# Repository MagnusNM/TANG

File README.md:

# TANG
Like RAMPS but for dumb shit

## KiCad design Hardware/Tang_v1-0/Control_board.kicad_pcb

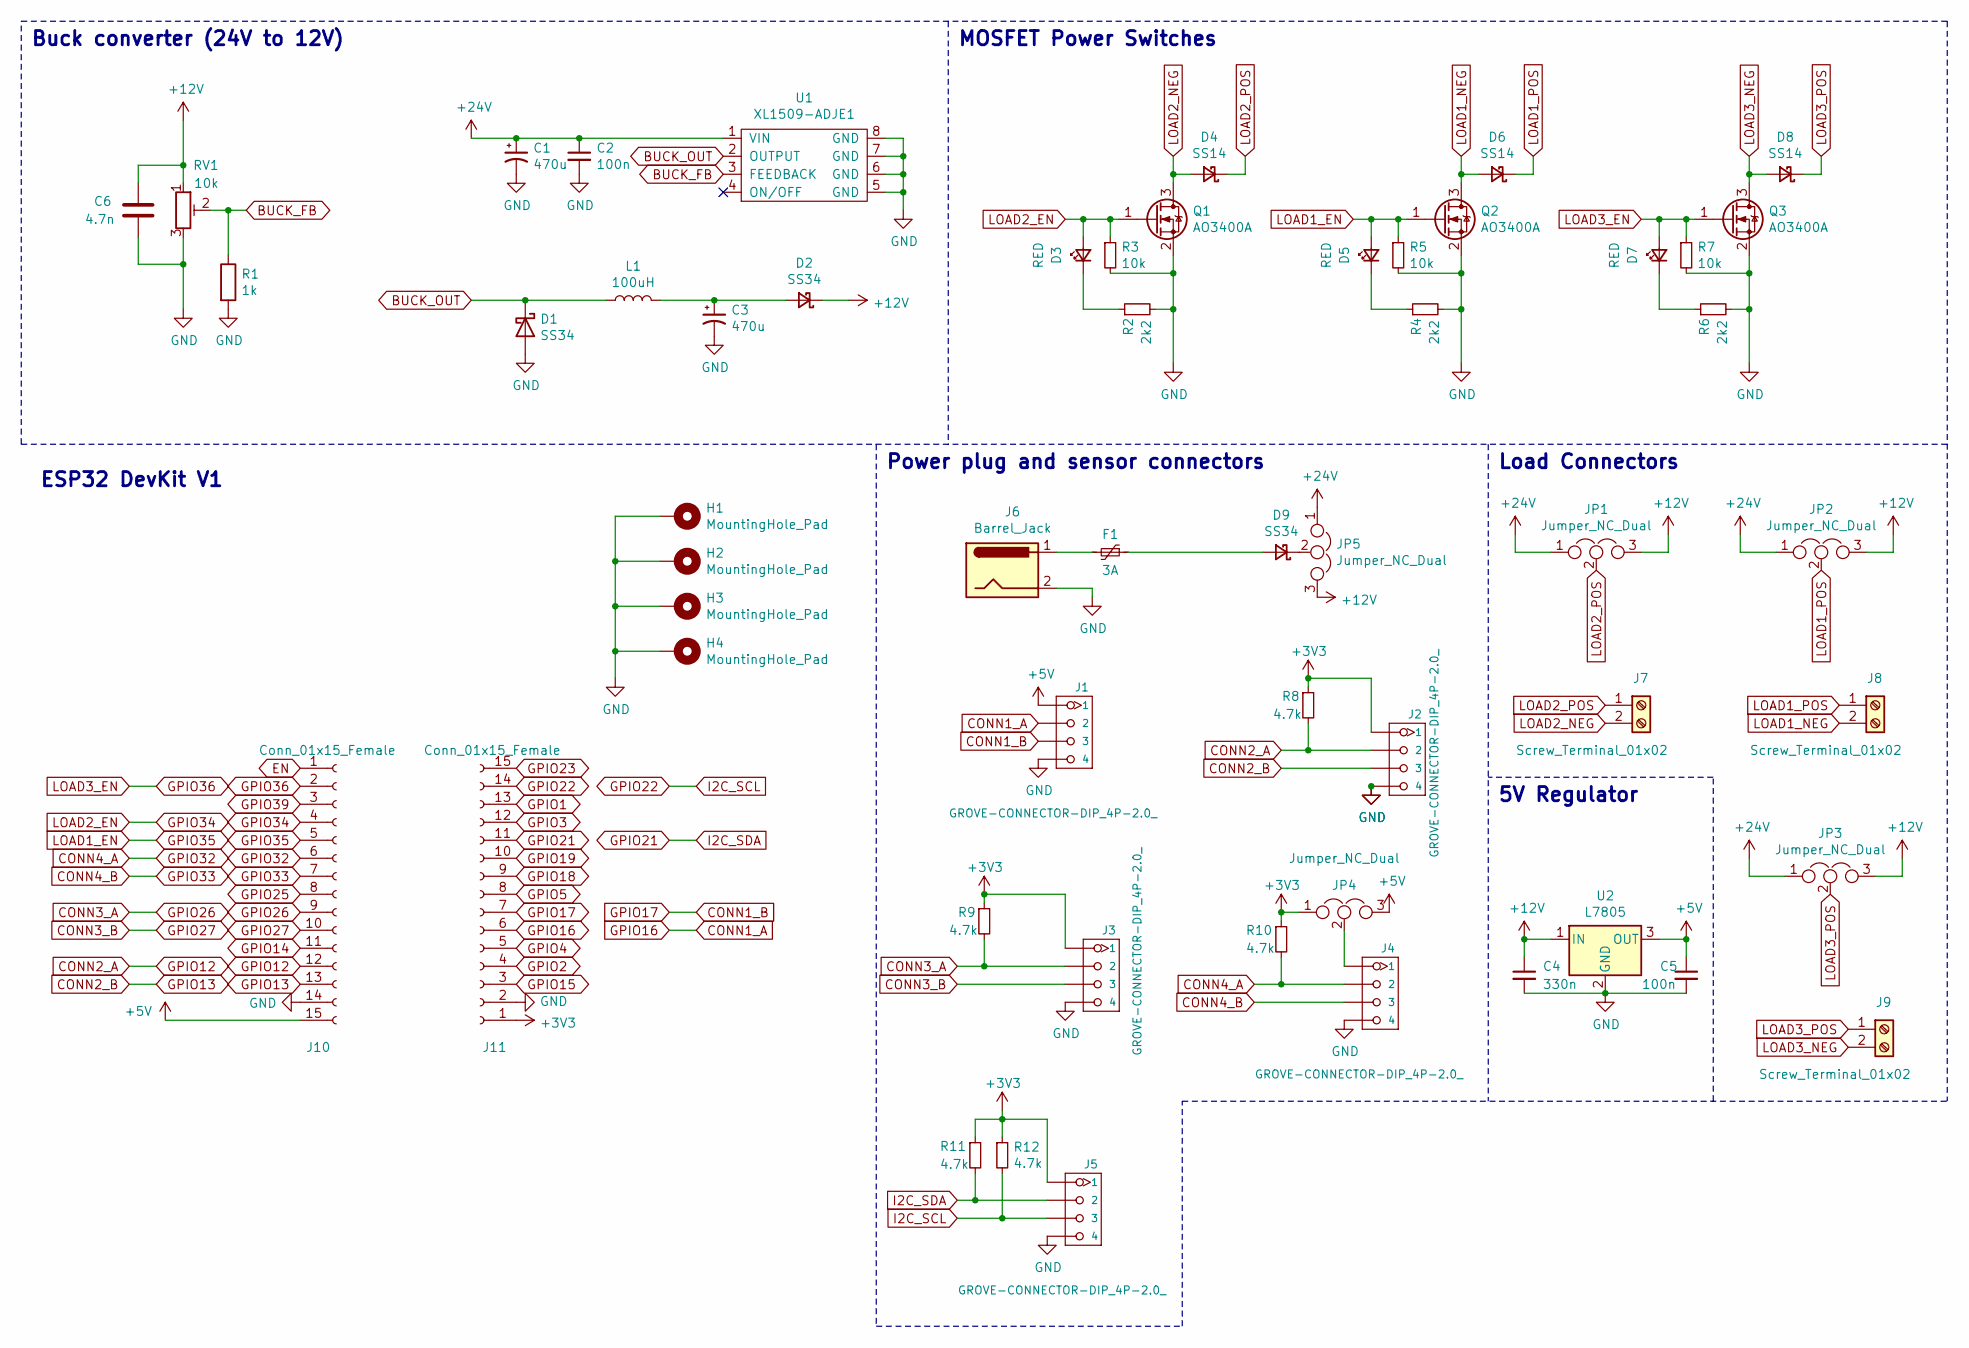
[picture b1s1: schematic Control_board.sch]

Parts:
C1, C3: 470u; C_Elec_10x10.2; LCSC Part # C3350
C2: 100n; C_0603_1608Metric; LCSC Part # C14663
C4: 330n; C_0805_2012Metric; LCSC Part # C1740
C5: 100n; C_0805_2012Metric; LCSC Part # C49678
C6: 4.7n; C_0402_1005Metric; LCSC Part # C1538
D1, D2, D9: SS34; D_SMA; LCSC Part # C8678
D3, D5, D7: RED; LED_0603_1608Metric; LCSC Part # C2286
D4, D6, D8: SS14; D_SMA; LCSC Part # C2480
F1: 3A; Fuse_1812_4532Metric; LCSC Part # C32404
H1, H2, H3, H4: MountingHole_Pad; MountingHole_3.2mm_M3_Pad_Via
J1, J2, J3, J4, J5: GROVE-CONNECTOR-DIP_4P-2.0_; NS-Tech_Grove_1x04_P2mm_Vertical
J6: Barrel_Jack; BarrelJack_Horizontal
J7, J8, J9: Screw_Terminal_01x02; TerminalBlock_Phoenix_MPT-0,5-2-2.54_1x02_P2.54mm_Horizontal
J10, J11: Conn_01x15_Female; PinSocket_1x15_P2.54mm_Vertical
JP1, JP2, JP3, JP4, JP5: Jumper_NC_Dual; PinHeader_1x03_P2.54mm_Vertical
L1: 100uH; Wuerth_7447211101; LCSC Part # C429814
Q1, Q2, Q3: AO3400A; SOT-23; LCSC Part # C344010
R1: 1k; R_0603_1608Metric; LCSC Part # C21190
R2, R4, R6: 2k2; R_0603_1608Metric; LCSC Part # C4190
R3, R5, R7: 10k; R_0603_1608Metric; LCSC Part # C25804
R8, R9, R10, R11, R12: 4.7k; R_0402_1005Metric; LCSC Part # C25900
RV1: 10k; Potentiometer_Bourns_3296P_Horizontal
U1: XL1509-ADJE1; SOP-8_3.9x4.9mm_P1.27mm; LCSC Part # C74192
U2: L7805; TO-263-2; LCSC Part # C15077

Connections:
+3V3: J2.1, J3.1, J5.1, J11.1, JP4.1, R8.1, R9.1, R10.1, R11.1, R12.1
+5V: C5.1, J1.1, J10.15, JP4.3, U2.3 (OUT)
+12V: C4.1, C6.1, D2.1 (K), JP1.3, JP2.3, JP3.3, JP5.3, RV1.1, U2.1 (IN)
+24V: C1.1, C2.1, JP1.1, JP2.1, JP3.1, JP5.1, U1.1 (VIN)
BUCK_FB: R1.1, RV1.2, U1.3 (FEEDBACK)
BUCK_OUT: D1.1 (K), L1.1, L1.3, U1.2 (OUTPUT)
CONN1_A: J1.2, J11.6
CONN1_B: J1.3, J11.7
CONN2_A: J2.2, J10.12, R8.2
CONN2_B: J2.3, J10.13
CONN3_A: J3.2, J10.9, R9.2
CONN3_B: J3.3, J10.10
CONN4_A: J4.2, J10.6, R10.2
CONN4_B: J4.3, J10.7
EN: J10.1
GND: C1.2, C2.2, C3.2, C4.2, C5.2, C6.2, D1.2 (A), H1.1, H2.1, H3.1, H4.1, J1.4, J2.4, J3.4, J4.4, J5.4, J6.2, J10.14, J11.2, Q1.2 (S), Q2.2 (S), Q3.2 (S), R1.2, R2.2, R3.2, R4.2, R5.2, R6.2, R7.2, RV1.3, U1.5 (GND), U1.6 (GND), U1.7 (GND), U1.8 (GND), U2.2 (GND)
GPIO1: J11.13
GPIO2: J11.4
GPIO3: J11.12
GPIO4: J11.5
GPIO5: J11.8
GPIO14: J10.11
GPIO15: J11.3
GPIO18: J11.9
GPIO19: J11.10
GPIO21: J5.2, J11.11, R11.2
GPIO22: J5.3, J11.14, R12.2
GPIO23: J11.15
GPIO25: J10.8
GPIO34: D3.2 (A), J10.4, Q1.1 (G), R3.1
GPIO35: D5.2 (A), J10.5, Q2.1 (G), R5.1
GPIO36: D7.2 (A), J10.2, Q3.1 (G), R7.1
GPIO39: J10.3
LOAD1_NEG: D6.2 (A), J8.2, Q2.3 (D)
LOAD1_POS: D6.1 (K), J8.1, JP2.2
LOAD2_NEG: D4.2 (A), J7.2, Q1.3 (D)
LOAD2_POS: D4.1 (K), J7.1, JP1.2
LOAD3_NEG: D8.2 (A), J9.2, Q3.3 (D)
LOAD3_POS: D8.1 (K), J9.1, JP3.2
unnamed: C3.1, D2.2 (A), L1.2
unnamed: D3.1 (K), R2.1
unnamed: D5.1 (K), R4.1
unnamed: D7.1 (K), R6.1
unnamed: D9.1 (K), JP5.2
unnamed: D9.2 (A), F1.1
unnamed: F1.2, J6.1
unnamed: J4.1, JP4.2

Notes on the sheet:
Buck converter (24V to 12V)
MOSFET Power Switches
Load Connectors
5V Regulator
Power plug and sensor connectors
ESP32 DevKit V1

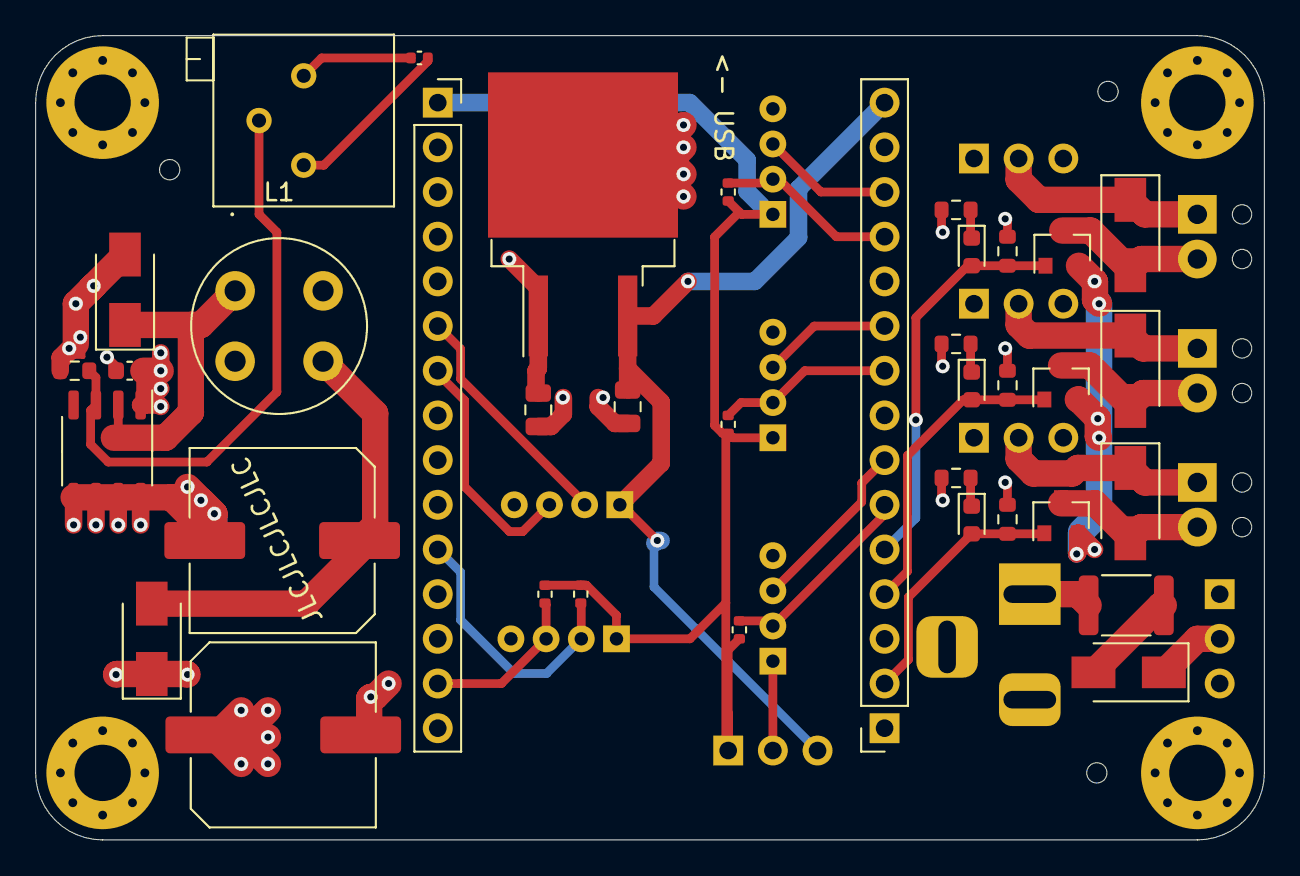
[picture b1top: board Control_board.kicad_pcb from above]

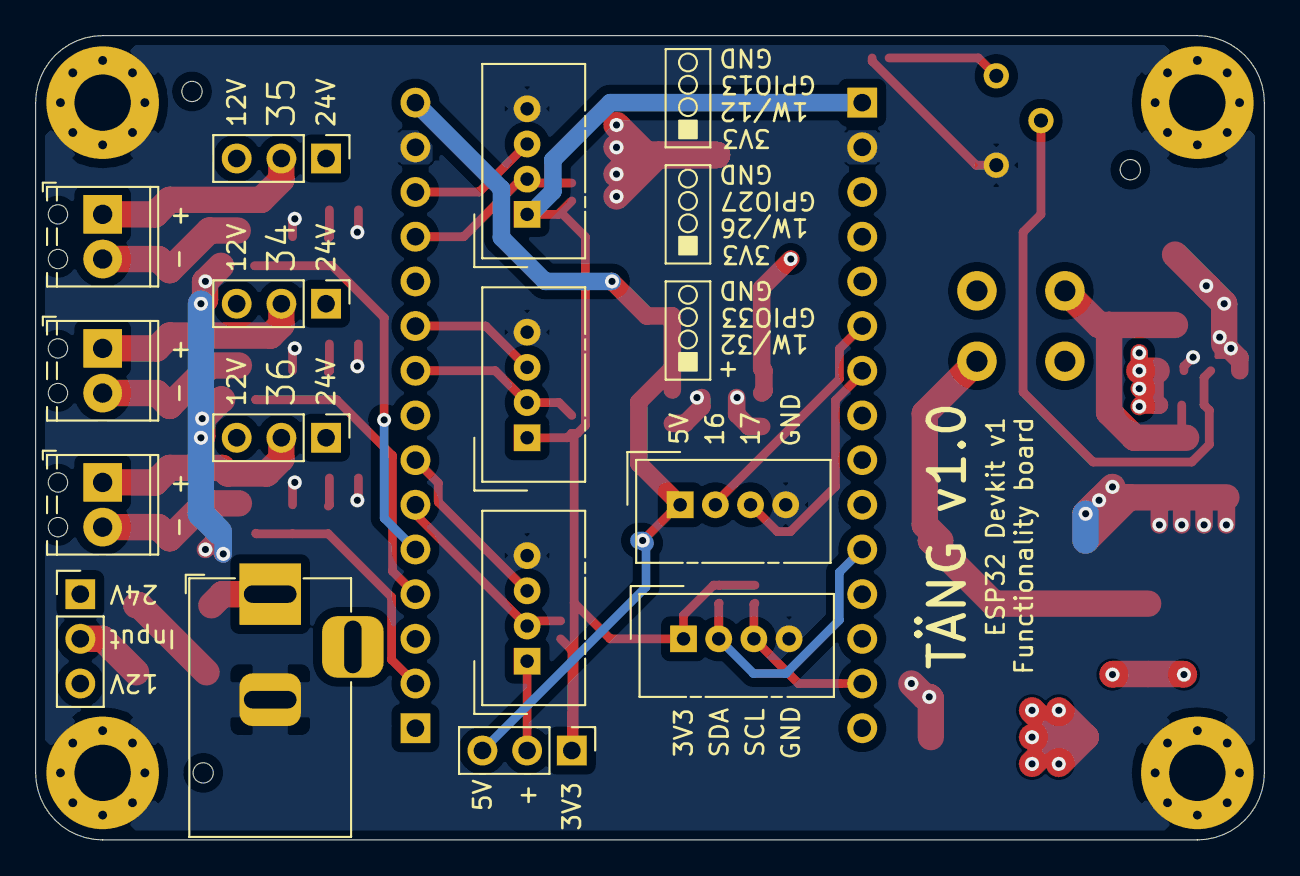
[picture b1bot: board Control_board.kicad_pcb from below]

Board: 4 copper layers, 69.8 x 45.7 mm, 55 parts (14 on the bottom side), 34 nets.

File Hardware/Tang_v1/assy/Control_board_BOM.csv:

Comment,Designator,Footprint,LCSC
470u,"C1,C3",Capacitor_SMD:C_Elec_10x10.2,C3350
100n,C2,Capacitor_SMD:C_0603_1608Metric,C14663
330n,C4,Capacitor_SMD:C_0805_2012Metric,C1740
100n,C5,Capacitor_SMD:C_0805_2012Metric,C49678
4.7n,C6,Capacitor_SMD:C_0402_1005Metric,C1538
RED,"D3,D5,D7",LED_SMD:LED_0603_1608Metric,C2286
SS14,"D4,D6,D8",Diode_SMD:D_SMA,C2480
SS34,"D1,D2,D9",Diode_SMD:D_SMA,C8678
3A,F1,Fuse:Fuse_1812_4532Metric,C32404
MountingHole_Pad,"H1,H2,H3,H4",MountingHole:MountingHole_3.2mm_M3_Pad_Via,
Conn_01x15_Female,"J10,J11",Connector_PinSocket_2.54mm:PinSocket_1x15_P2.54mm_Vertical,
GROVE-CONNECTOR-DIP_4P-2.0_,"J1,J2,J3,J4,J5",Connector:NS-Tech_Grove_1x04_P2mm_Vertical,
Barrel_Jack,J6,Connector_BarrelJack:BarrelJack_Horizontal,
Screw_Terminal_01x02,"J7,J8,J9","TerminalBlock_Phoenix:TerminalBlock_Phoenix_MPT-0,5-2-2.54_1x02_P2.54mm_Horizontal",
Jumper_NC_Dual,"JP1,JP2,JP3,JP4,JP5",Connector_PinHeader_2.54mm:PinHeader_1x03_P2.54mm_Vertical,
100uH,L1,RasmusKiCadLibrary:Wuerth_7447211101,
AO3400A,"Q1,Q2,Q3",Package_TO_SOT_SMD:SOT-23,C344010
1k,R1,Resistor_SMD:R_0603_1608Metric,C21190
4.7k,"R8,R9,R10,R11,R12",Resistor_SMD:R_0402_1005Metric,C25900
2k2,"R2,R4,R6",Resistor_SMD:R_0603_1608Metric,C4190
10k,"R3,R5,R7",Resistor_SMD:R_0603_1608Metric,C25804
10k,RV1,Potentiometer_THT:Potentiometer_Bourns_3296P_Horizontal,
XL1509-ADJE1,U1,Package_SO:SOP-8_3.9x4.9mm_P1.27mm,C74192
L7805,U2,Package_TO_SOT_SMD:TO-263-2,C15077

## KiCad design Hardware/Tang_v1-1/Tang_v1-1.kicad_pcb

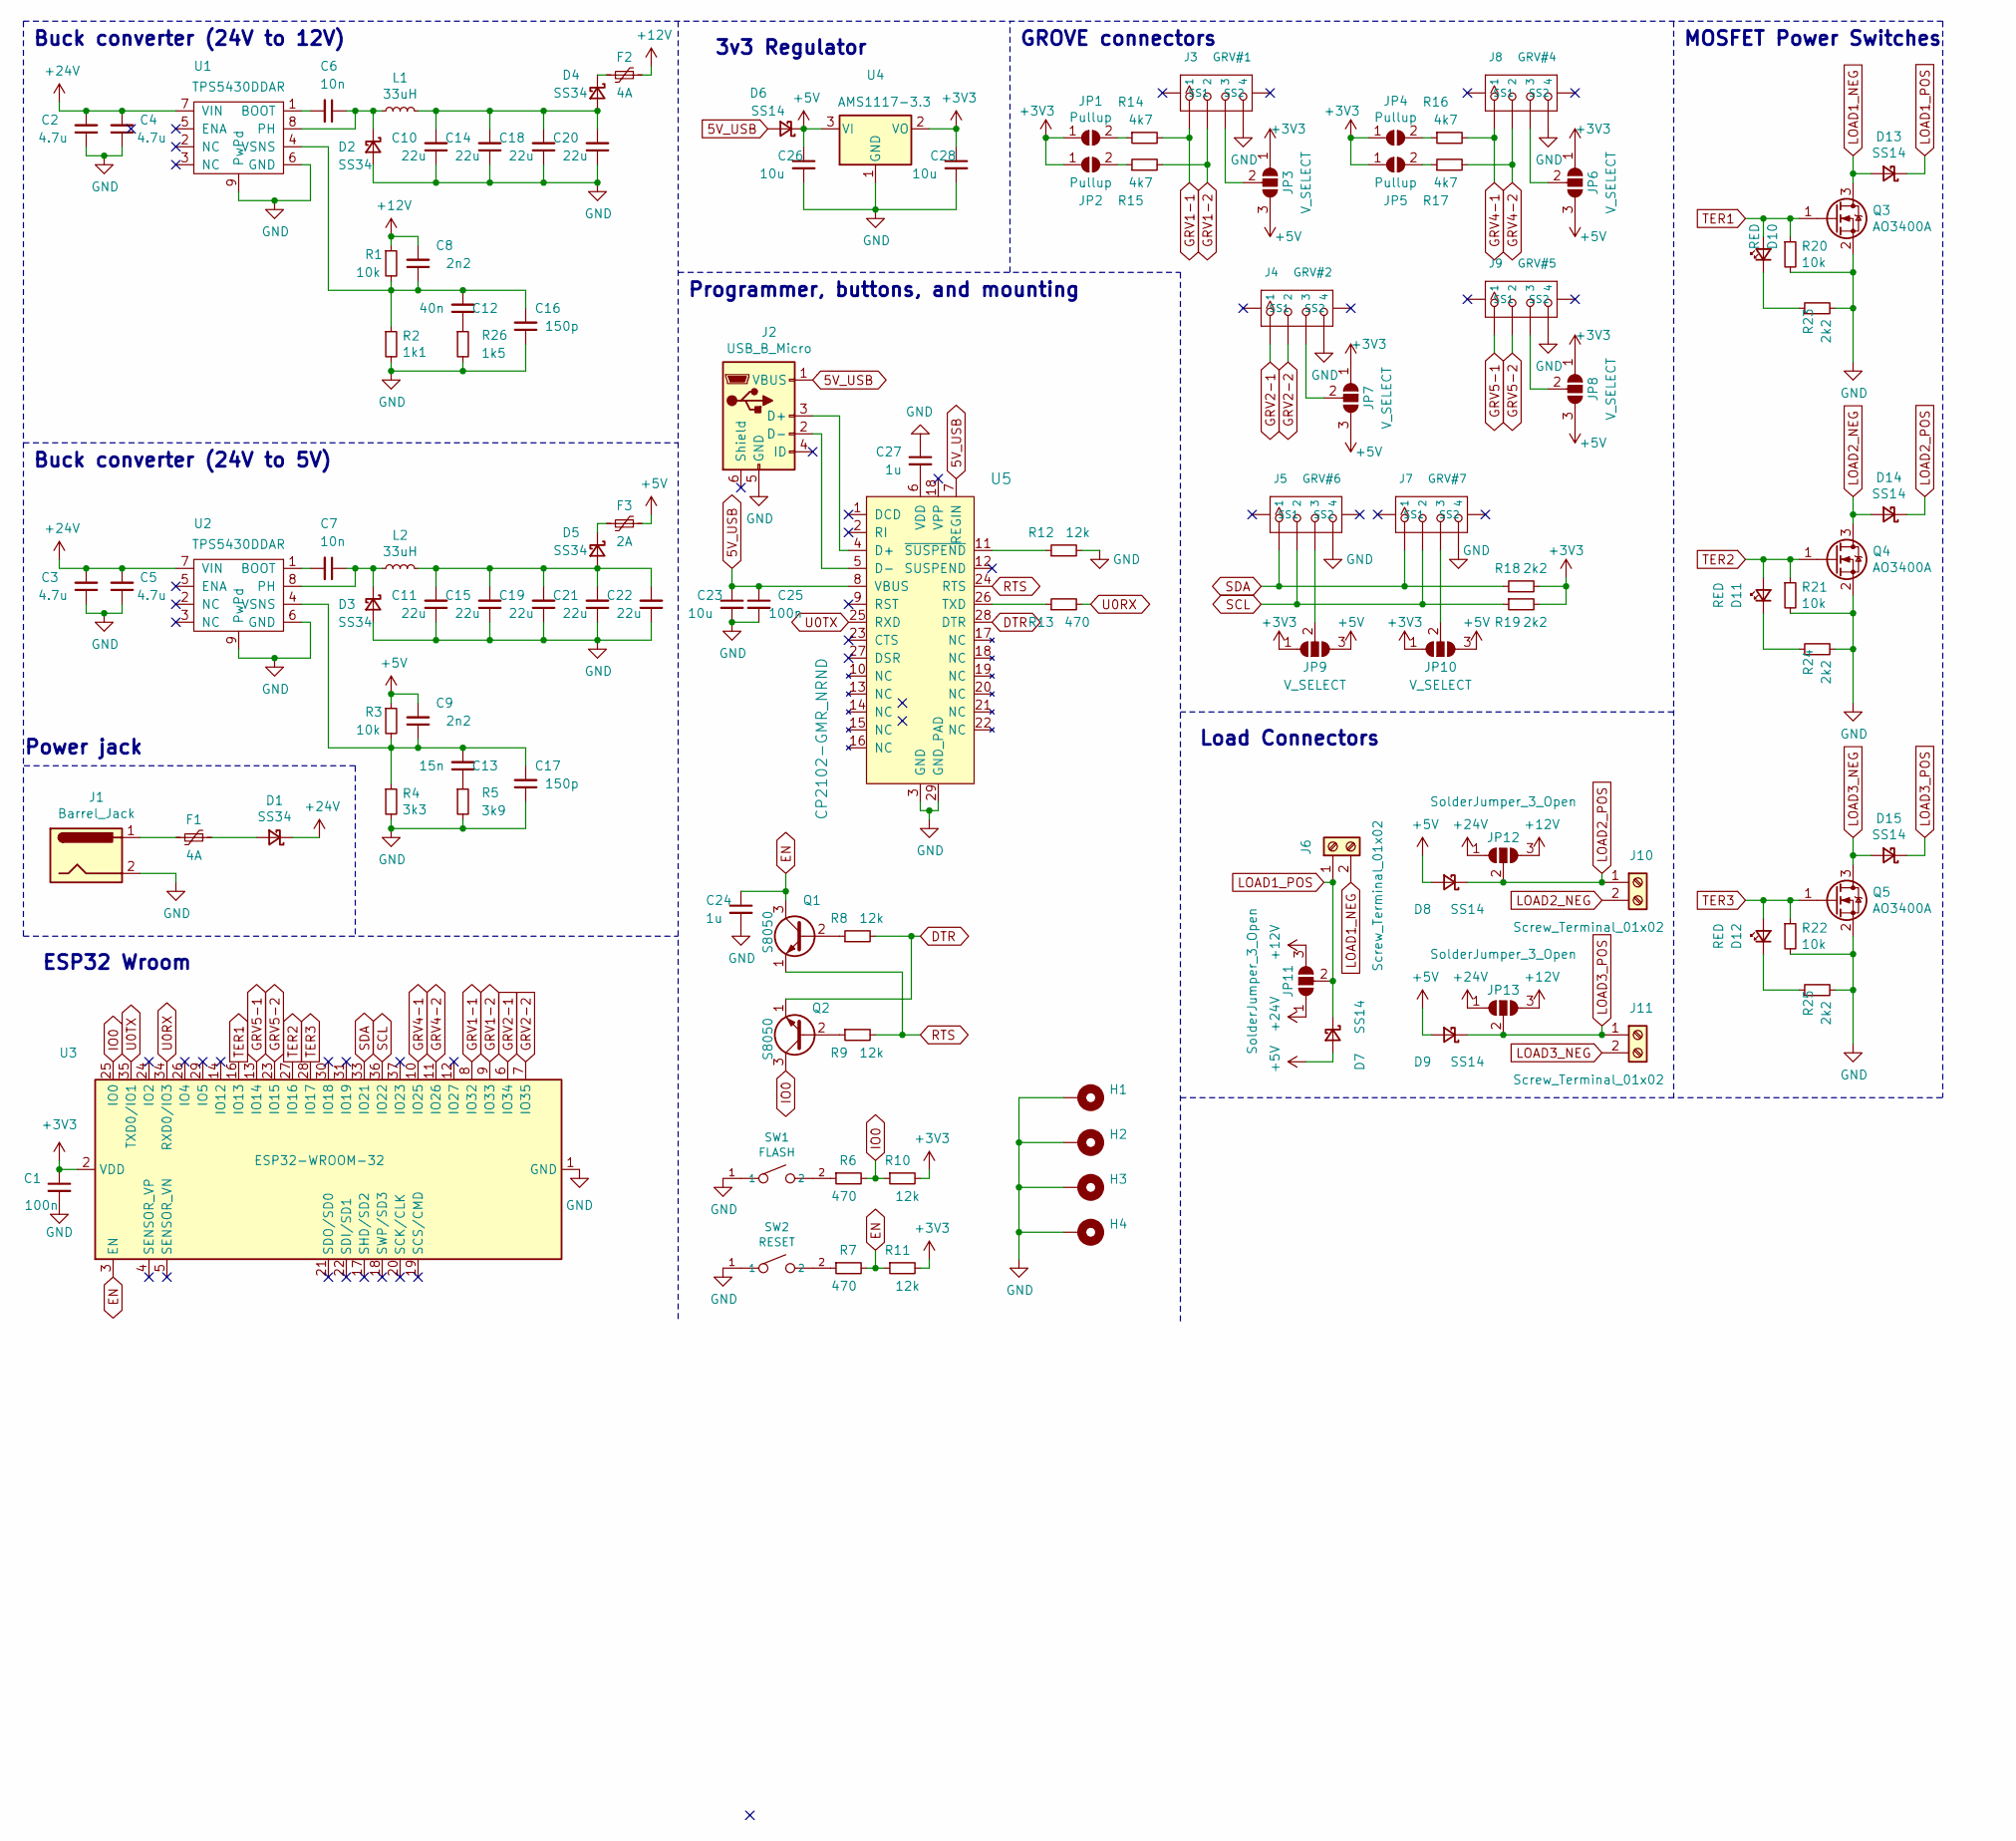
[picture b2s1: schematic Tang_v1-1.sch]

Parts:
C1, C25: 100n; C_0603_1608Metric; LCSC C14663
C2, C3, C4, C5: 4.7u; C_1206_3216Metric; LCSC Part # C29823
C6, C7: 10n; C_0603_1608Metric; LCSC Part # C57112
C8, C9: 2n2; C_0603_1608Metric; LCSC Part # C1604
C10, C11, C14, C15, C18, C19, C20, C21, C22: 22u; C_0805_2012Metric; LCSC Part # C45783
C12: 40n; C_0805_2012Metric; LCSC Part # C502151
C13: 15n; C_0603_1608Metric; LCSC Part # C1596
C16, C17: 150p; C_0603_1608Metric; LCSC Part # C1594
C23: 10u; C_0805_2012Metric; LCSC C15850
C24, C27: 1u; C_0603_1608Metric; LCSC C15849
C26, C28: 10u; C_0805_2012Metric; LCSC Part # C15850
D1: SS34; D_SMA; LCSC Part # C8678
D2, D3, D4, D5: SS34; D_SMA; LCSC C8678
D6, D7, D8, D9: SS14; D_SMA; LCSC C2480
D10, D11, D12: RED; LED_0603_1608Metric; LCSC Part # C2286
D13, D14, D15: SS14; D_SMA; LCSC Part # C2480
F1, F2: 4A; Fuse_1812_4532Metric; LCSC Part # C960026
F3: 2A; Fuse_1812_4532Metric; LCSC Part # C269134
H1, H2, H3, H4: MountingHole_Pad; MountingHole_3.2mm_M3_Pad_Via
J1: Barrel_Jack; BarrelJack_Horizontal
J2: USB_B_Micro; USB_Micro-B_Molex-105017-0001; LCSC C10418
J3: GRV#1; GROVE 4 pin 90deg SMD
J4: GRV#2; GROVE 4 pin 90deg SMD
J5: GRV#6; GROVE 4 pin 90deg SMD
J6, J10, J11: Screw_Terminal_01x02; TerminalBlock_Phoenix_MKDS-1,5-2-5.08_1x02_P5.08mm_Horizont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
J7: GRV#7; GROVE 4 pin 90deg SMD
J8: GRV#4; GROVE 4 pin 90deg SMD
J9: GRV#5; GROVE 4 pin 90deg SMD
JP1, JP2, JP4, JP5: Pullup; SolderJumper-2_P1.3mm_Open_RoundedPad1.0x1.5mm
JP3, JP6, JP7, JP8, JP9, JP10: V_SELECT; SolderJumper-3_P1.3mm_Open_RoundedPad1.0x1.5mm
JP11, JP12, JP13: SolderJumper_3_Open; SolderJumper-3_P1.3mm_Open_RoundedPad1.0x1.5mm
L1, L2: 33uH; L_TDG_11.5x10x4mm
Q1, Q2: S8050; SOT-23; LCSC C2146
Q3, Q4, Q5: AO3400A; SOT-23; LCSC Part # C20917
R1, R3: 10k; R_0603_1608Metric; LCSC C25804
R2: 1k1; R_0603_1608Metric; LCSC C22764
R4: 3k3; R_0603_1608Metric; LCSC C22978
R5: 3k9; R_0603_1608Metric; LCSC C23018
R6, R7, R13: 470; R_0603_1608Metric; LCSC Part # C23179
R8, R9, R10, R11, R12: 12k; R_0603_1608Metric; LCSC Part # C22790
R14, R15, R16, R17: 4k7; R_0603_1608Metric; LCSC Part # C23162
R18, R19, R23, R24, R25: 2k2; R_0603_1608Metric; LCSC Part # C4190
R20, R21, R22: 10k; R_0603_1608Metric; LCSC Part # C25804
R26: 1k5; R_0603_1608Metric; LCSC C22843
SW1: FLASH; SW_Push_SPST_NO_Alps_SKRK; MPN B3U-1000P-2P-SMD; LCSC C115357
SW2: RESET; SW_Push_SPST_NO_Alps_SKRK; MPN B3U-1000P-2P-SMD; LCSC C115357
U1, U2: TPS5430DDAR; HSOP-8-1EP_3.9x4.9mm_P1.27mm_EP2.41x3.1mm; LCSC C9864
U3: ESP32-WROOM-32; LCSC C82899
U4: AMS1117-3.3; SOT-223-3_TabPin2; LCSC C6186
U5: CP2102-GMR_NRND; VFQFN-28-1EP_5x5mm; MPN CP2102-GMR; Digi-Key_PN 336-1160-1-ND

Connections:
5V_USB: C23.1, C25.1, D6.2 (A), J2.1 (VBUS), U5.7 (REGIN), U5.8 (VBUS)
+3V3: C1.1, C28.1, JP1.1 (A), JP2.1 (A), JP3.1 (A), JP4.1 (A), JP5.1 (A), JP6.1 (A), JP7.1 (A), JP8.1 (A), JP9.1 (A), JP10.1 (A), R10.2, R11.2, R18.2, R19.2, U3.2 (VDD), U4.2 (VO)
+5V: C9.2, C26.1, D6.1 (K), D7.2 (A), D8.2 (A), D9.2 (A), F3.1, JP3.3 (B), JP6.3 (B), JP7.3 (B), JP8.3 (B), JP9.3 (B), JP10.3 (B), R3.1, U4.3 (VI)
+12V: C8.2, F2.1, JP11.3 (B), JP12.3 (B), JP13.3 (B), R1.1
+24V: C2.2, C3.2, C4.2, C5.2, D1.1 (K), JP11.1 (A), JP12.1 (A), JP13.1 (A), U1.7 (VIN), U2.7 (VIN)
DTR: Q2.1 (E), R8.2, U5.28 (DTR)
EN: C24.1, Q1.3 (C), R7.2, R11.1, U3.3 (EN)
GND: C1.2, C2.1, C3.1, C4.1, C5.1, C10.1, C11.1, C14.1, C15.1, C16.1, C17.1, C18.1, C19.1, C20.1, C21.1, C22.1, C23.2, C24.2, C25.2, C26.2, C27.1, C28.2, D2.2 (A), D3.2 (A), H1.1, H2.1, H3.1, H4.1, J1.2, J2.5 (GND), J3.4, J4.4, J5.4, J7.4, J8.4, J9.4, Q3.2 (S), Q4.2 (S), Q5.2 (S), R2.2, R4.2, R5.2, R12.2, R20.2, R21.2, R22.2, R23.2, R24.2, R25.2, R26.2, SW1.1, SW2.1, U1.6 (GND), U1.9 (PwPd), U2.6 (GND), U2.9 (PwPd), U3.1 (GND), U3.15 (GND), U3.38 (GND), U3.39 (GND), U4.1 (GND), U5.3 (GND), U5.29 (GND_PAD)
GRV1-1: J3.1, R14.2, U3.8 (IO32)
GRV1-2: J3.2, R15.2, U3.9 (IO33)
GRV2-1: J4.1, U3.6 (IO34)
GRV2-2: J4.2, U3.7 (IO35)
GRV4-1: J8.1, R16.2, U3.10 (IO25)
GRV4-2: J8.2, R17.2, U3.11 (IO26)
GRV5-1: J9.1, U3.13 (IO14)
GRV5-2: J9.2, U3.23 (IO15)
IO0: Q2.3 (C), R6.2, R10.1, U3.25 (IO0)
LOAD1_NEG: D13.2 (A), J6.2, Q3.3 (D)
LOAD1_POS: D7.1 (K), D13.1 (K), J6.1, JP11.2 (C)
LOAD2_NEG: D14.2 (A), J10.2, Q4.3 (D)
LOAD2_POS: D8.1 (K), D14.1 (K), J10.1, JP12.2 (C)
LOAD3_NEG: D15.2 (A), J11.2, Q5.3 (D)
LOAD3_POS: D9.1 (K), D15.1 (K), J11.1, JP13.2 (C)
unnamed: C6.1, D2.1 (K), L1.1, U1.8 (PH)
unnamed: C6.2, U1.1 (BOOT)
unnamed: C7.1, D3.1 (K), L2.1, U2.8 (PH)
unnamed: C7.2, U2.1 (BOOT)
unnamed: C10.2, C14.2, C18.2, C20.2, D4.2 (A), L1.2
unnamed: C11.2, C15.2, C19.2, C21.2, C22.2, D5.2 (A), L2.2
unnamed: C12.1, R26.1
unnamed: C8.1, C12.2, C16.2, R1.2, R2.1, U1.4 (VSNS)
unnamed: C13.1, R5.1
unnamed: C9.1, C13.2, C17.2, R3.2, R4.1, U2.4 (VSNS)
unnamed: C27.2, U5.6 (VDD)
unnamed: D1.2 (A), F1.1
unnamed: D4.1 (K), F2.2
unnamed: D5.1 (K), F3.2
unnamed: D10.1 (K), R23.1
unnamed: D11.1 (K), R24.1
unnamed: D12.1 (K), R25.1
unnamed: F1.2, J1.1
unnamed: J2.2 (D-), U5.5 (D-)
unnamed: J2.3 (D+), U5.4 (D+)
unnamed: J3.3, JP3.2 (C)
unnamed: J4.3, JP7.2 (C)
unnamed: J5.3, JP9.2 (C)
unnamed: J7.3, JP10.2 (C)
unnamed: J8.3, JP6.2 (C)
unnamed: J9.3, JP8.2 (C)
unnamed: JP1.2 (B), R14.1
unnamed: JP2.2 (B), R15.1
unnamed: JP4.2 (B), R16.1
unnamed: JP5.2 (B), R17.1
unnamed: Q1.2 (B), R8.1
unnamed: Q2.2 (B), R9.1
unnamed: R6.1, SW1.2
unnamed: R7.1, SW2.2
unnamed: R12.1, U5.11 (~SUSPEND)
unnamed: R13.1, U5.26 (TXD)
RTS: Q1.1 (E), R9.2, U5.24 (RTS)
SCL: J5.2, J7.2, R19.1, U3.36 (IO22)
SDA: J5.1, J7.1, R18.1, U3.33 (IO21)
TER1: D10.2 (A), Q3.1 (G), R20.1, U3.16 (IO13)
TER2: D11.2 (A), Q4.1 (G), R21.1, U3.27 (IO16)
TER3: D12.2 (A), Q5.1 (G), R22.1, U3.28 (IO17)
U0RX: R13.2, U3.34 (RXD0/IO3)
U0TX: U3.35 (TXD0/IO1), U5.25 (RXD)

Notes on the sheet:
Buck converter (24V to 12V)
MOSFET Power Switches
Load Connectors
Programmer, buttons, and mounting
ESP32 Wroom
3v3 Regulator
Buck converter (24V to 5V)
GROVE connectors
Power jack

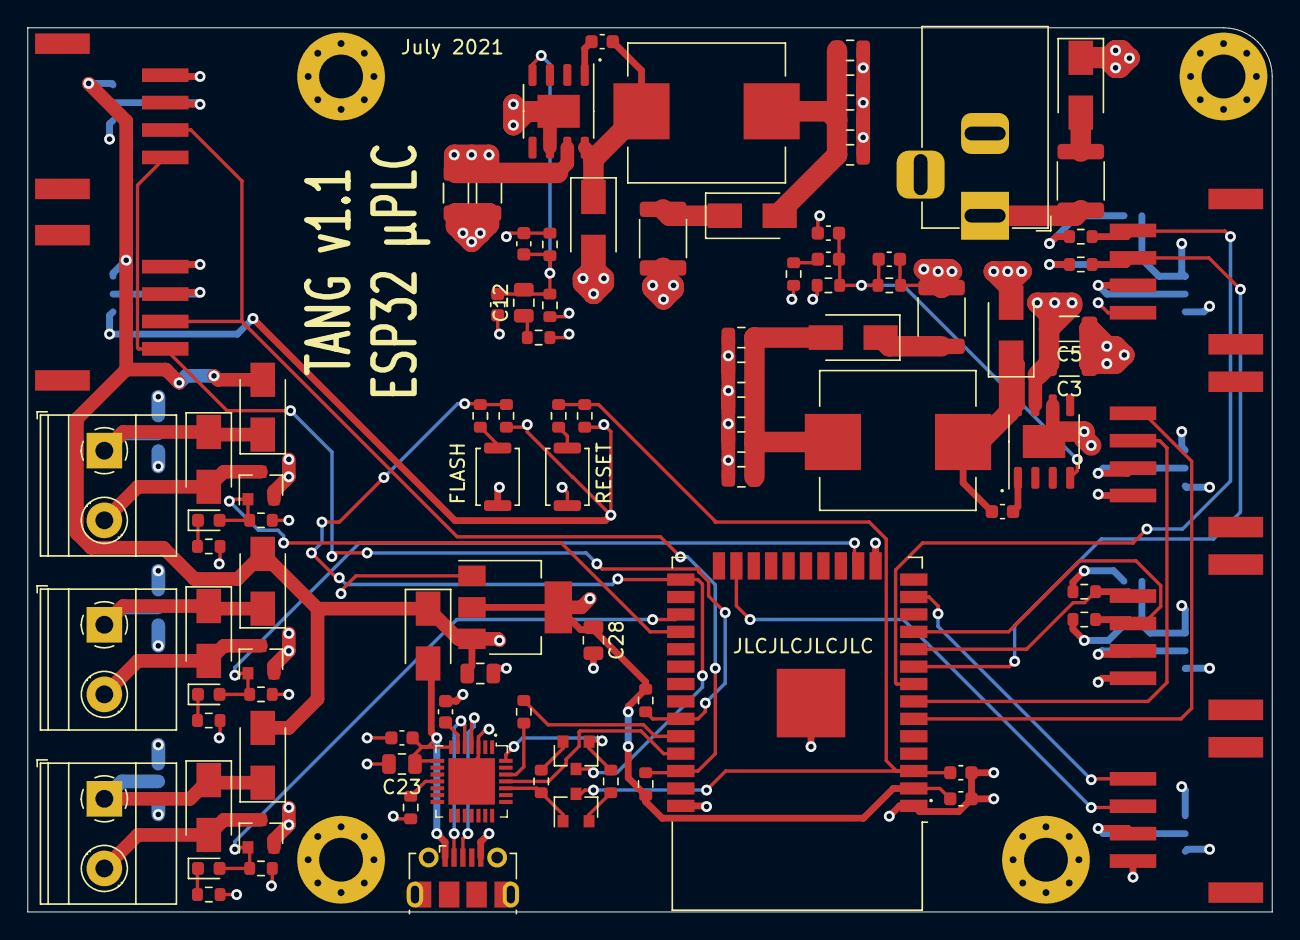
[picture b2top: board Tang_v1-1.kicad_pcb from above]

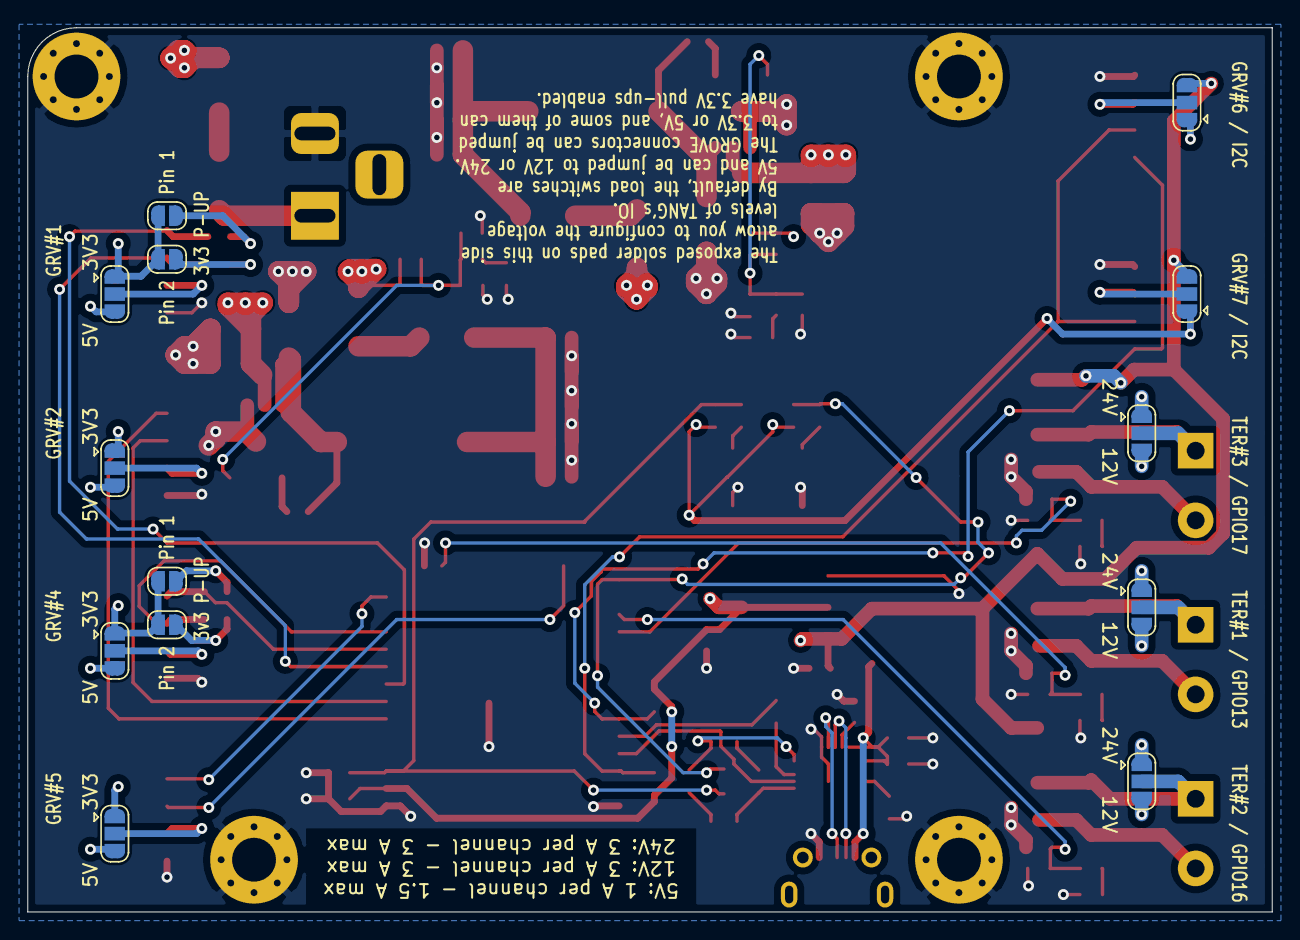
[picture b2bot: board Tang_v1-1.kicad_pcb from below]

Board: 4 copper layers, 90.8 x 64.5 mm, 114 parts (13 on the bottom side), 67 nets.

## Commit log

2021-06-26 Got pushing to work, cleaned repo up and changed main file name
2021-07-06 Folder structure
2021-07-06 Changed folder name to Hardware
2021-07-06 Adding TANG v1 to repo
2021-07-06 Removed login stuff
2021-07-06 Adding mining controller to firmware repo
2021-07-07 Started on Tang v2
2021-07-08 Added power switches
2021-07-13 Added v1.1 and v2 WIP
